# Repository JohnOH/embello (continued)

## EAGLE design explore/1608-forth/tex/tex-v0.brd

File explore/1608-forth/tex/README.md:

This area is for the "Tiny Extender", a HyTiny with an "Extender PCB".

The PCB combines a HyTiny (STM32F103), optional RFM69CW, optional SPI flash,
and female FTDI host header (i.e. to talk to and program a JeeNode Zero, etc).

### Hardware

See the EAGLE files and derived documentation:

* `tex-v0.sch` - EAGLE 7.6 schematic
* `tex-v0.pdf` - EAGLE 7.6 schematic, as PDF
* `tex-v0.brd` - EAGLE 7.6 board layout
* `tex-v0.png` - EAGLE 7.6 board layout, as image

The PDF shows all the relevant pin assignments.

Further down below is a section about a alternate board, called the Blue Pill.

### Software

Tex (i.e. the software) runs on Mecrisp 2.3.0 or later, with console I/O over
USB.  The code for the "Serial USB driver for Forth" is in the `../suf/` area.

To load the software onto the HyTiny, you need to connect power and the PA9 +
PA10 pins to a USB-serial adapter. On the host side, you need to be running
Folie v2 or later. Use "raw" mode (-r) with a BUB or similar, or the default
telnet mode if going through a "SerPlus" interface.

> **Note:** there is a way to bypass the build steps below, which consists of
> uploading a complete pre-built image (`usb-common.hex`) into the HyTiny, but
> it tends to lag the latest releases at times - YMMV!  To try it out and take
> advantage of Folie's nifty upload-from-the-web feature, replace everything
> below with the following, all on one line:
>
>     !u https://raw.githubusercontent.com/jeelabs/embello/
>           master/explore/1608-forth/suf/usb-common.hex
>
> Then, disconnect and plug the HyTiny back in using its USB jack. Now you can
> continue with the "Update" section below to install the rest of the code.

Here is a rough outline of the steps involved to install tex from scratch:

* use Folie's `!u` command to upload `f103-mecrisp` into the HyTiny
* there are several crucial details (with ISP pressed, briefly press RESET)
* after a succesful reflash, the HyTiny now runs Forth on its USART1 interface
* go to the `../suf/` area so you can append the USB driver to it
* enter `!s f-common.fs` to send the driver, there should be no errors
* after reset, you will no longer have serial access to the HyTiny
* unplug the HyTiny and re-connect using its USB jack
* if all went well, you should be able to restart Folie and connect again
* you are now running Forth over USB, but with very little support code loaded
* the `eraseflash` word has been redefined so that the USB driver stays intact

We're almost done... hang in there!

* go back to the `../tex/` area (can be done inside Folie, using `!cd ...`)
* load the board definitions, by entering this in Folie: `!s board.fs`
* now, the basic board peripherals and pin definitions are in flash
* you can always reset the dictionary by typing `<<<board>>>`
* load some useful drivers and library code, using `!s core.fs`
* now, the RFM69 and OLED + graphics are loaded, ready for use
* at any time, to reset the Forth dict to just usb+board+core, type `<<<core>>>`

That's it. You now have a fairly complete environment running over USB. See the
`board.fs` and `core.fs` source code to find out what has been included.

For a (very) long list of what's currently defined, type `words`. For a shorter
list, you can type `list`. The last item shown is also the last word defined in
flash memory (RAM definitions always end up at the beginning of these listings).

### Reset

A USB-based console setup has some quirks, because a reset in Forth causes the
entire system to restart, losing the current USB session and re-enumerating it.
This has a similar effect as unplugging and re-plugging the HyTiny.

Right now, on MacOS this is fairly harmless, because the re-enumerated device
shows up with the same name again within a second or so, and Folie will then
automatically pick it up and re-connect.

On Linux and Windows, this is (as of end Nov 2016) not yet the case. You will
need to quit Folie, and restart it, selecting the correct USB port again - which
may have gotten a new name (i.e. `COM<N+1>`, resp. `/dev/ttyACM<N+1>`).

Resets can be generated by various words in Mecrisp Forth:

* `reset` (of course), as well as `eraseflash` and `eraseflashfrom`
* calling a previously-defined cornerstone, e.g. `<<<board>>>` or `<<<core>>>`

All of these, apart from the explicit `reset`, are due to the fact that the
Forth dictionary is a linked list, and that major surgery on it requires Mecrisp
to re-initialise itself from scratch. Including the USB driver, in this context.

Due to the disruptive nature of resets when using the console over USB, it is
not possible to send files from Folie with the above "resetting commands" in
them. Instead, you need to comment those out, type them in manually, and _then_
send the file with the remaining code.

### Telnet

Another detail to be aware of is Folie's "telnet" vs "raw" (-r) mode. In its
default telnet mode, Folie does not control the DTR/RTS pins, since these only
work with directly-attached USB-serial devices, and only when the O/S _and_ the
USB-serial interface work together fully. With net sockets, there are no pins.

Telnet is an "in-band" protocol, i.e. it uses the hex "FF" byte as special
escape to insert special messages (and to escape genuine FF bytes in the data).

Mecrisp does not know about telnet, but due to some init overrides, there is an
extra layer or decoding once `board.fs` has been installed and restarted. For
this reason, once tex has been set up, you should talk to it in Folie _without_
the "-r" option. But only then. Before that stage, all console I/O needs to be
done with in raw mode - this includies the initial `!u ...` reflash and the `!s
...` commands given to folie to send everything up to and including `board.fs`.

It's often easy to see when you get it wrong, because you'll get "funny" chars.

In short: you have to be aware of "-r" for this initial setup, but once tex is
fully installed and being used on an day-to-day basis, it's no longer needed.

### SerPlus

Tex includes a `serplus` mode, which turns the HyTiny into a USB-serial
interface (using the host FTDI connector). The difference with a BUB and other
USB-serial interfaces, is that it interprets (and strips) in-band telnet
escapes. With SerPlus, Folie can control the DTR and the RTS pin, and both reset
_and_ re-flash an attached STM32 µC board. The way to start this is to enter
`serplus` as Forth command. To switch back to Forth, you have to press the RESET
button on the HyTiny.

See the `explore/1649-f103/serplus/` folder for more information about SerPlus.

As of this writing (Nov 2016), switching to SerPlus causes a reset. See above...

### Updates

At some point there will be updates to `board.fs` or `core.fs`, or to some of
the files they include. Since all this code sits above the USB driver layer,
it can in fact be updated through USB. Here is how to update `board.fs`:

* type `eraseflash` at the Forth prompt
* the unit resets, you'll lose the USB session and may need to relaunch Folie
* when connected again, enter `words` to see all definitions scroll by
* the last two entries should be called `init` and `eraseflash`
* go to the `../tex/` area (as before, this can be done inside Folie)
* re-install the updated board code, using `!s board.fs`
* if you enter `words` now, the last item listed should be `<<<board>>>`
* board has now been replaced, but we'll need to re-install `core.fs` as well
* continue with the steps below...

To replace only the `core.fs` code and leave `board.fs` intact, start here:

* type `<<<board>>>` at the Forth prompt
* the unit resets, you'll lose the USB session and may need to relaunch Folie
* when connected again, enter `words` to see all definitions scroll by
* the last entry should be called `<<<board>>>`
* go to the `../tex/` area (as before, this can be done inside Folie)
* re-install the updated core code, using `!s core.fs`
* if you enter `words` now, the last item listed should be `<<<core>>>`

Excellent, you're done - you have a shiny new version of tex installed in flash.

Note that updates to the USB driver or to Mecrisp Forth itself cannot be done
through the USB connection. You'll need to hook up the serial port again, and
follow the "Software" instructions above, same as when installing from scratch.

### Blue Pill

There is another very common low-cost F103 board, which is often called the
"Blue Pill". It differs slightly from the HyTiny in shape and size, but also has
some other differences:

* it's a 48-pin µC, vs HyTiny's 36-pin, and has more I/O pins and h/w interfaces
* it reports 64K flash, vs 128K for the HyTiny (but rumours say it's still 128K)
* the LED is on PC13, vs PA1 on the HyTiny
* the ISP pin (BOOT0) is a yellow jumper instead of a push-button
* there's no USB-pull-up via a transistor to trigger USB re-enumeration
* instead, PA12 must be controlled internally via GPIO, using different code

That last difference makes it harder to re-use exactly the same code for both
boards. But there's a way out: since the flash sizes differ, this has been used
to differentiate between the two and create a single `f-common.fs` setup which
will auto-detect on startup and control USB accordingly.

So if you keep these differences in mind, you should be able to adapt the above
information and get the USB console working on the Blue Pill as well.

There is now a `../g6u` area for generic boards like the Blue Pill, running over
USB and with pin definitions up to 64-pin chips. Here is a transcript of loading
those definitions once the USB console is working:

```
$ cd ../g6u
$ folie -r
Select the serial port:
  1: /dev/cu.Bluetooth-Incoming-Port
  2: /dev/cu.usbmodem322F2211
? 2
Enter '!help' for additional help, or ctrc-d to quit.
[connected to /dev/cu.usbmodem322F2211]
  ok.
eraseflash
Erase block at  00006800  from Flash
[...]
Finished. Reset
[disconnected] no such file or directory
[connected to /dev/cu.usbmodem322F2211]
  ok.
!s board.fs
1> board.fs 5: ( board start: ) 00006800  ok.
5> io.fs 11: Redefine bit.  ok.
1> board.fs 29: Redefine init.  ok.
1> board.fs 38: ( board end, size: ) 00008064 6244  ok.
!s core.fs
1> core.fs 4: cr compiletoflash
 ok.
1> core.fs 5: ( core start: ) 00008800  ok.
1> core.fs 13: ( core end, size: ) 0000A7EC 8172  ok.
  ok.
hello 64 KB <g6u> 322F221E ram: 17456 free flash: 20480 free  ok.
```

You can copy this `g6u/` area as starting point for your own explorations and
projects. Note that you may have to adjust the relative directory references in
`board.fs` and `core.fs` if you copy it to a different location.

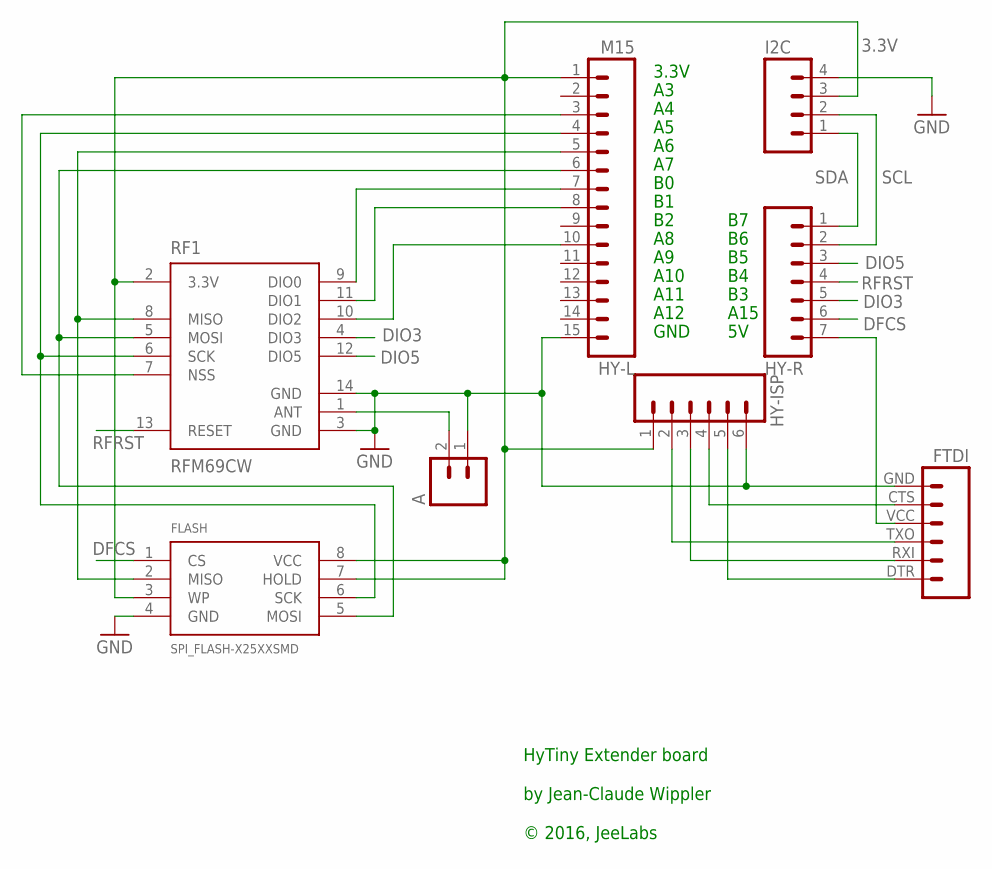
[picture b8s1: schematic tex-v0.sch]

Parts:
A: M021X02_NO_SILK; 1X02_NO_SILK
FLASH: SPI_FLASH-X25XXSMD; SO08
FTDI: FTDI_BASICPTH; FTDI_BASIC
HY-ISP: M06NO_SILK_FEMALE_PTH; 1X06_NO_SILK
HY-L: M15; 1X15
HY-R: M07; 1X07
I2C: M041X04_NO_SILK; 1X04_NO_SILK
RF1: RFM69CW; RFM69CW-XXXS2

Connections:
3.3V: FLASH.3 (WP), FLASH.7 (HOLD), FLASH.8 (VCC), HY-ISP.1, HY-L.1, I2C.3, RF1.2 (3.3V)
DFCS: FLASH.1 (CS), HY-R.6
DIO3: HY-R.5, RF1.4 (DIO3)
DIO5: HY-R.3, RF1.12 (DIO5)
GND: A.1, FLASH.4 (GND), FTDI.GND (6), HY-ISP.6, HY-L.15, I2C.4, RF1.3 (GND), RF1.14 (GND)
unnamed: FLASH.2 (MISO), HY-L.5, RF1.8 (MISO)
unnamed: FLASH.5 (MOSI), HY-L.6, RF1.5 (MOSI)
unnamed: FLASH.6 (SCK), HY-L.4, RF1.6 (SCK)
unnamed: HY-L.3, RF1.7 (NSS)
unnamed: FTDI.VCC (4), HY-R.7
unnamed: HY-L.7, RF1.9 (DIO0)
unnamed: HY-L.8, RF1.11 (DIO1)
unnamed: A.2, RF1.1 (ANT)
unnamed: FTDI.RXI (2), HY-ISP.3
unnamed: FTDI.TXO (3), HY-ISP.2
unnamed: FTDI.CTS (5), HY-ISP.4
unnamed: FTDI.DTR (1), HY-ISP.5
unnamed: HY-L.10, RF1.10 (DIO2)
RFRST: HY-R.4, RF1.13 (RESET)
SCL: HY-R.2, I2C.2
SDA: HY-R.1, I2C.1

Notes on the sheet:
3.3V
A10
A11
A12
GND
A15
HyTiny Extender board by Jean-Claude Wippler © 2016, JeeLabs

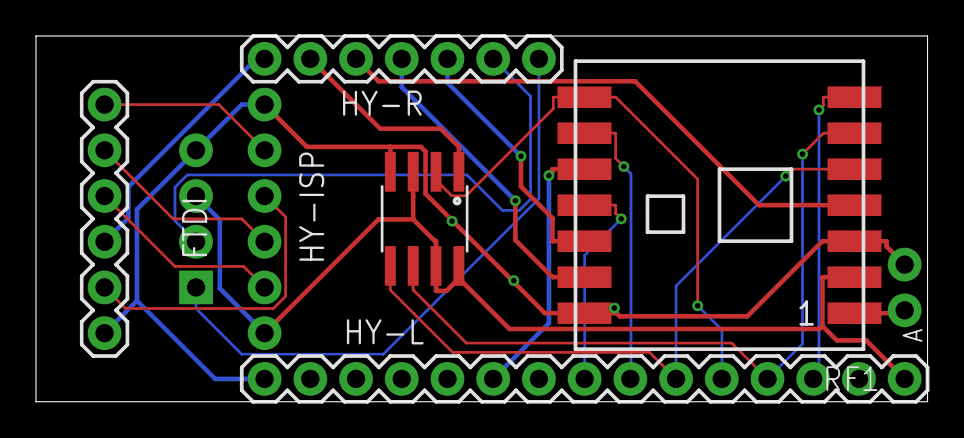
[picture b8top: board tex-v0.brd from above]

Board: 2 copper layers, 49.5 x 20.3 mm, 8 parts (1 on the bottom side), 21 nets.

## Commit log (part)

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2016-12-08 tweaks
2016-12-09 remove lux readings from sensor data
2016-12-10 add credits
2016-12-10 rename +adc to adc-init
2016-12-10 rename +i2c to i2c-init
2016-12-10 rename [+1]i2c to pwm-(de)init
2016-12-10 rename +dac to dac-init
2016-12-10 rename [+-]timer to timer-(de)init
2016-12-10 rename +tft to tft-init
2016-12-10 rename +uart to uart-init
2016-12-11 adjust vendor info
2016-12-11 fix dir name
2016-12-11 minor name change
2016-12-12 update to latest code
2016-12-13 fix olimexino and maplemini usb images
2016-12-13 fix port103z usb image
2016-12-14 add new IO test
2016-12-14 add e-dim.fs example, move cornerstone definition
2016-12-14 cleanup
2016-12-14 add new optimised IO words (thx, Matthias!)
2016-12-17 tweak
2016-12-17 add disassemblers from mecrisp distro
2016-12-18 add Si570 driver
2016-12-18 add node about forgetram
2016-12-19 auto hz/khz/mhz switching
2016-12-21 rename jnz to jz3, add l052 core
2016-12-22 change pin for JNZ rev3
2016-12-23 update blink for multi-rev use
2016-12-23 add led demo for weblog post
2016-12-23 add bme280 demo for weblog
2016-12-26 add quotation experiment
2016-12-26 increase both buffer sizes to 1024
2016-12-26 renames
2016-12-26 capitalise constants
2016-12-27 make USB key? poll multi-tasker friendly
2016-12-27 update images
2016-12-29 Comment tweak
2017-01-04 systick-correction after switching cpu speed
2017-01-04 Allow ms to pass token in multitasking.
2017-01-04 Cleaning up comments
2017-01-05 more timing tests
2017-01-05 rename all "rf69[-.]*" words to "rf[-.]*"
2017-01-05 add compiletoram, fixes #30
2017-01-05 make ms multi-tasker aware, closes #31
2017-01-05 add systick-hz? - see #29
2017-01-05 add swd-deinit and rename -jtag to jtag-deinit, closes #28
2017-01-07 Wake boot-task on keypress
2017-01-07 ignore top-level other/ dir for unpublished stuff
2017-01-08 rename current tex pcb files to v0
2017-01-08 whitespace cleanup
2017-01-08 move e-<name> to ex/<name>.fs and final.fs to freeze.fs
2017-01-08 reload all code instead of just main
2017-01-08 define backlight pin for LCD
2017-01-08 add note about USB
2017-01-08 add USB builds for two more F103 boards
2017-01-09 add high-flash erase/write test
2017-01-12 Catch up
    Need to get interrupt working.
2017-01-13 add text-v0 front and back photos
2017-01-13 rename prc1 and add new prc2
2017-01-13 add pin defs and adc readouts
2017-01-14 add button handlers
2017-01-14 fix formatting
2017-01-14 add more pins
2017-01-14 add heartbeat LED
2017-01-14 fix pwm zero case, now fully off
2017-01-14 typo
2017-01-14 crude stepper trial
2017-01-15 tweak for 12V use
2017-01-15 add servo motion
2017-01-15 Initial commit in this repository
2017-01-15 missing reference to TSL4531, fixes #37
2017-01-18 start work on console access gateway
2017-01-19 lower RSSI threshold from $C4 to $A0
2017-01-22 various
2017-01-22 remove all duplicates of "always.fs"
2017-01-23 Update pid.md
    typos
2017-01-25 Create timed.md
    Initial commit for documentation of timed.fs
2017-01-25 update to board/core conventions
2017-01-25 Interface cleanups
2017-01-25 cleanups
2017-01-26 fix long-standing USB back-to-back packet bug
2017-01-26 bump input ring buffer so it can handle at least a full mecrisp input buffer
2017-01-26 update USB builds to Mecrisp 2.3.3 w/ USB back-to-back fix
2017-01-27 crude solution for shedding output when host is not reading it
2017-01-27 simplify
2017-01-27 change license
2017-01-29 simple rx/tx test between two nodes
2017-01-30 go fmt cleanup
2017-01-30 back-pressure in USB works!
2017-01-30 update usb firmware images
2017-02-02 add TMP102 driver
2017-02-04 add new exploration
2017-02-04 Exploring interrupts
2017-02-04 EXT Interrupts are a puzzle
2017-02-05 Working on interrupts
2017-02-05 increase us timing slightly
2017-02-05 move some init code into core.fs
2017-02-05 clarify directory structure, see #39
2017-02-06 add comment about flash page size, closes #39
2017-02-06 Prepare for GitHub Pages
2017-02-06 Set theme jekyll-theme-minimal
2017-02-06 Create CNAME
2017-02-07 add home page docs
2017-02-07 add tools and some headers
2017-02-07 update docs with homepage ref
2017-02-07 OLED display tweaks
2017-02-07 tweaks to the rf69 driver and switch to rf- prefix
2017-02-07 faster spi implementation
2017-02-07 add support for stml052 uart2
2017-02-07 remove some differences
2017-02-07 remove init differences
2017-02-07 Interrupts finally working
    Unclear why PA2 responds differently to PB9. PB9 works whereas PA2
    doesn’t!
2017-02-07 Interrupt PA2 now working
    I haven’t found out why the change.
2017-02-08 Tidy up comments
2017-02-08 custom SCSS for small tweak
2017-02-08 override layout, add documentation to sidebar
2017-02-08 navigation tweaks
2017-02-08 move PWM docs to new structure
2017-02-08 remove duplicate link
2017-02-08 fix links and typo
2017-02-08 add some I2C docs
2017-02-08 doc tweaks
2017-02-09 split varint tests off into separate file; fix tests
2017-02-09 add comments to testing code
2017-02-10 add jnz hardware info
2017-02-10 add more hardware info
2017-02-10 Looking at Timers
2017-02-10 prepare for doc extractor tool
2017-02-11 started on a new documentation expander
2017-02-11 expansion is working
2017-02-11 jnz3 fs20 ook receiver
2017-02-11 speed up of micros function
2017-02-12 transform doc files in-place
2017-02-12 add root and quiet flags
2017-02-12 add Makefile to auto-expand docs using new "docex" tool
2017-02-12 fix readme example
2017-02-12 add bit-banged SPI docs
2017-02-12 rename oled.fs to ssd1306.fs
2017-02-12 add ssd1306 docs
2017-02-12 add gpio docs
2017-02-12 fix io@ to return 0 or -1
2017-02-12 doc tweak
2017-02-12 add "-u" source url option
2017-02-12 add bme280 sensor docs
2017-02-12 rename "-adc" to "adc-deinit"
2017-02-12 add adc docs
2017-02-12 add sleep docs
2017-02-12 add more hal and adc docs
2017-02-12 try subdir listing
2017-02-12 subdirs not usable without index
2017-02-12 more tables
2017-02-12 show images in board list
2017-02-12 oops, forgot images
2017-02-12 resize small images
2017-02-13 Output cleanups
2017-02-13 improvement fast micros. Add 32MHz full speed
2017-02-13 small refinement in main loop timing
2017-02-14 rename >+pkt to _pkt and add varint docs
2017-02-14 update docs
2017-02-14 oops
2017-02-14 include some notes from the Redmine wiki
2017-02-14 add readme
2017-02-14 add url
2017-02-15 add hycore144 docs
2017-02-15 add rev4 files
2017-02-17 add jnz4 test setup
2017-02-17 add hex file
2017-02-18 Timer interrupt
    Test RSSI to Sync Match timing within bounds.
2017-02-19 add release hex file
2017-02-19 add quick loader over SPI, still using dummy data
2017-02-19 fix readme
2017-02-22 BOOT0 is 5V-tolerant
2017-02-22 Move IRQ vectors
2017-02-22 add JNZ rev3 hex image
2017-02-23 add a full 2.3.5 image for usb-common
2017-02-23 add a full 2.3.5 image for serial
2017-02-23 rename, image is for all F103s
2017-02-24 simplify .gitignore mask
2017-02-24 add release hex for jnz rev1
2017-02-24 add basic rotary encoder tests
2017-02-24 Add always.fs to JZ1
2017-02-24 Add always.fs to JZ1 (#48)
2017-02-24 Add AES-128 modules
2017-02-24 Add AES-128 module doc
2017-02-24 reorg of AES source and docs
2017-02-24 oops, add missing file
2017-02-25 add SevenW as contributor (OOK and AES)
2017-02-25 replace with working example code
2017-02-25 add trivial tone demo
2017-03-01 fix unbalanced stack
2017-03-02 add delay and a pull-up note, see #51
2017-03-02 more tweaks for #51
2017-03-02 keep older versios of the "spezial" Mecrisp build around for reference
2017-03-02 minor reorg
2017-03-02 add exti demo
2017-03-02 add more rotary encoder examples
2017-03-03 more rotary encoder examples
2017-03-06 add missing rot8 code
2017-03-12 add EZ80 retro project
2017-03-13 add memory r/w access
2017-03-13 add serial hello test
2017-03-13 add 512K static RAM
2017-03-14 add flash init code
2017-03-14 start with flash setup
2017-03-15 split powerup and flash code
2017-03-16 crude cp/m launch from ram disk works
2017-03-16 working setup
2017-03-18 adjust memory map
2017-03-18 ram disk now loaded from flash
2017-03-18 add ram version check
2017-03-18 custom core.fs
2017-03-18 fix version check
2017-03-18 replace stat with hexsave
2017-03-20 reorg
2017-03-21 add multi-tasking example
2017-03-22 Moved libraries to flib/any
2017-03-22 Back to original version
2017-03-22 move pid/timed.md files to docs/ area
2017-03-22 try SD card readout
2017-03-22 add sdcard write and size calculation
2017-03-22 add periodic timer demo
2017-03-23 add spi bus pinout
2017-03-25 spi + dma working, but wrong cmd data being read
2017-03-25 first successful block read across SPI w/ DMA
2017-03-25 cannot get spi2/dma restart to work
2017-03-25 fixed CPHA mixup, SPI/DMA now working
2017-03-26 add FAT16 disk access
2017-03-26 eZ80 now reads from a FAT-mapped file
2017-03-26 move bios to $FA00, fix zdi pin drive
2017-03-27 new A..F disk map, C..F are now 1440K
2017-03-27 add virtual disk write support
2017-03-27 add filename lookup
2017-03-27 move SD and FAT code to flib/spi/sdcard.fs
2017-03-27 add mapdisk "jukebox" utility
2017-03-28 simplify file mapping calls
2017-03-28 make uart2 multi-tasker aware
2017-03-29 fix definition order
2017-03-29 try out interrupt-driven serial port bridging
2017-03-29 switch to irq + task wakeup for usart-to-usb data
2017-03-31 better request codes
2017-03-31 looks like the new boot setup is working
2017-03-31 getflash & putflash working
2017-04-02 split dev.fs into pokemon.fs and vdisk.fs
2017-04-04 work around timed branch offsets for M0+, thx @gea
2017-04-04 formatting changes
2017-04-15 Add Silicon Labs driver
2017-04-24 add new pcb design files
2017-04-26 Checkpoint
2017-04-27 modified v2 pcb pinouts
2017-04-28 add wr1280k ram test
2017-04-28 add images
2017-04-28 fix LED pin and image
2017-04-28 use button to break out of terminal loop
2017-05-01 update cores
2017-05-01 remove superfluous "cr" words
2017-05-01 expand tabs to spaces
2017-05-01 clean up formatting
2017-05-01 always switch off PLL before goint to 72 MHz - closes #54
2017-05-01 minor tweaks and new usb firmware images
2017-05-01 some reorgs to reduce flash memory usage
2017-05-02 rebuild usb images with board & core included
2017-05-04 start work on rfterm
2017-05-04 add remote/local switching and packet decode
2017-05-04 set up project
2017-05-04 implement packet reply logic
2017-05-04 Replace broken stm32f4/io.fs with working one based off stm32l0 version.
2017-05-05 Add stm32f4/timer.fs
2017-05-05 Finalize timeouts
2017-05-06 Add N=1 case
2017-05-06 Fix missing endof
2017-05-06 enhance .v in hexdump
2017-05-06 reverst chipid, etc reorg of Mat 1st
2017-05-06 shorten titles to avoid wrapping
2017-05-06 rf69 driver enhancements
2017-05-06 comment tweaks
2017-05-06 enhance docs
2017-05-06 bme280 enhancements
2017-05-07 expand tabs
2017-05-08 copy utility code from mecrisp with some examples
2017-05-08 add random demo
2017-05-09 fix bme reset, fixes #70
2017-05-09 updated cordic code from Matthias
2017-05-10 fix bme reset round 2, add unit test, fixes #72
2017-05-10 add profiler and routes demo code
2017-05-11 better build instructions, fixes #73
2017-05-16 multitask w/ IRQ
    Add documentation (and two helper words) to document the correct way to
    handle continuing a task from an interrupt
2017-05-16 Teach the bitbang I²C driver about clock stretching
2017-05-16 i2c-xfer only left nack on stack when probing
2017-05-16 i2c-init left the counter on the stack
2017-05-17 add to credits
2017-05-19 start on rf73 driver, simple recv working
2017-05-19 clean up receive messages
2017-05-19 add send code
2017-05-19 fix missing -spi on send and reset to rx
2017-05-20 fix whitespace
2017-05-20 rf console experiments
2017-05-25 Add stm32f4/adc.fs
2017-05-25 Bring stm32f4/hal.fs in line with the stm32f1 version
2017-05-25 Add buffered uart2 input for stm32f4
2017-05-25 Add pullup variants for OMODE-*-OD io modes
2017-05-25 add some docs for F4 additions
2017-05-31 fix BRR register offset, closes #81
2017-06-17 Fix credits
    *Nobody* spells my name correctly.
